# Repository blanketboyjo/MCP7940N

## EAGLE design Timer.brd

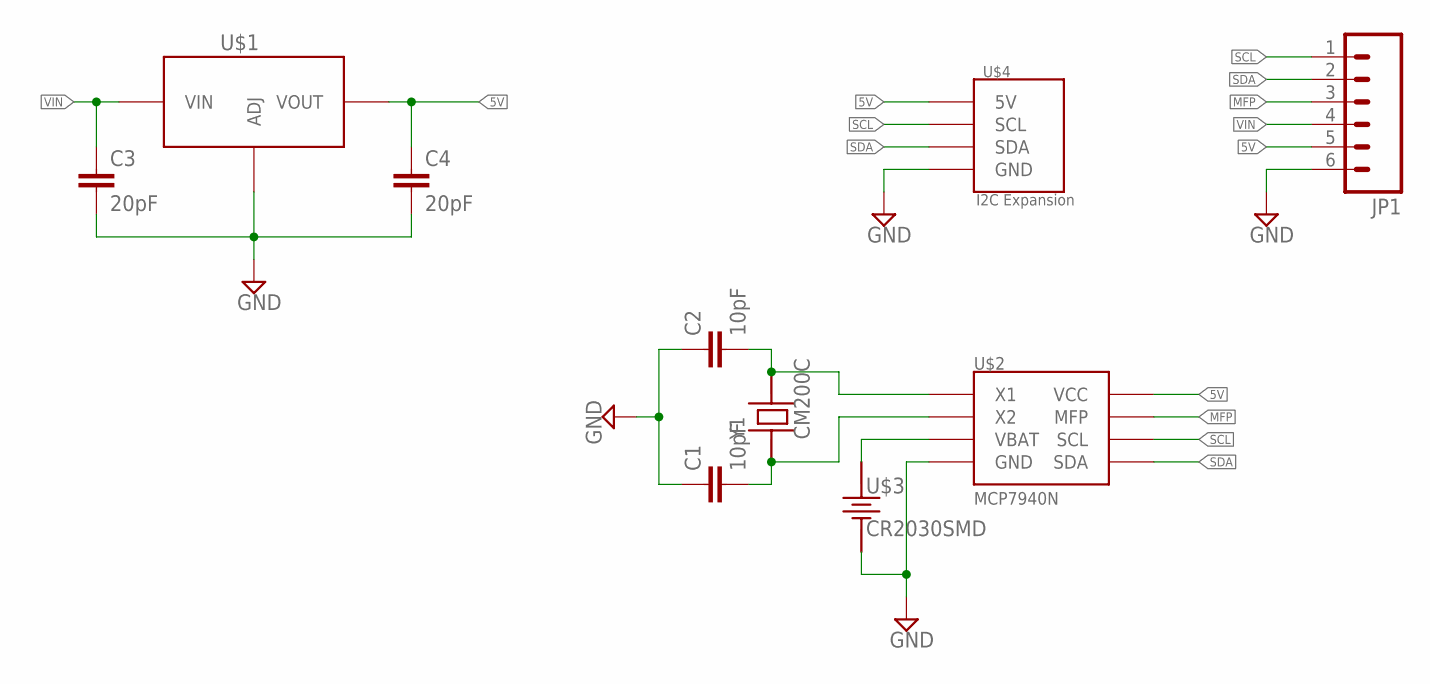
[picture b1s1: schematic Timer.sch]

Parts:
C1, C2: 10pF; 0603-CAP
C3, C4: 20pF; 0603-CAP
JP1: M06SILK_FEMALE_PTH; 1X06
U$1: LM1117; SOT223
U$2: MCP7940NSOIC-8; SOIC-8
U$3: CR2030SMD
U$4: I2CEXPANSION; JST-4-PTH-VERT
Y1: CM200C; CM2##

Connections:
5V: C4.1, JP1.5, U$1.P2 (VOUT), U$1.P4 (VOUT), U$2.VCC, U$4.1 (5V)
GND: C1.1, C2.1, C3.2, C4.2, JP1.6, U$1.P1 (ADJ), U$2.GND, U$3.GND (NEG), U$3.GND1 (NEG), U$4.4 (GND)
MFP: JP1.3, U$2.MFP
unnamed: U$2.VBAT, U$3.POS
unnamed: C2.2, U$2.X1, Y1.4
unnamed: C1.2, U$2.X2, Y1.1
SCL: JP1.1, U$2.SCL, U$4.2 (SCL)
SDA: JP1.2, U$2.SDA, U$4.3 (SDA)
VIN: C3.1, JP1.4, U$1.P3 (VIN)

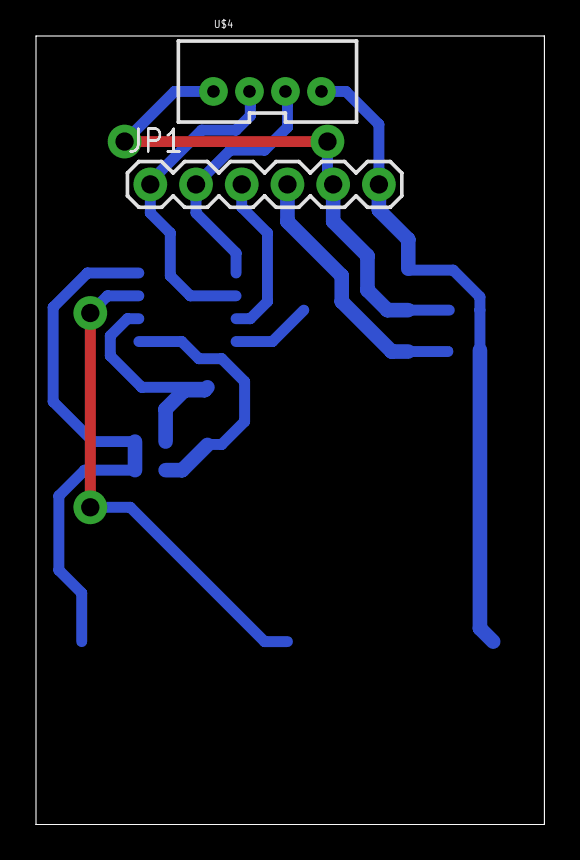
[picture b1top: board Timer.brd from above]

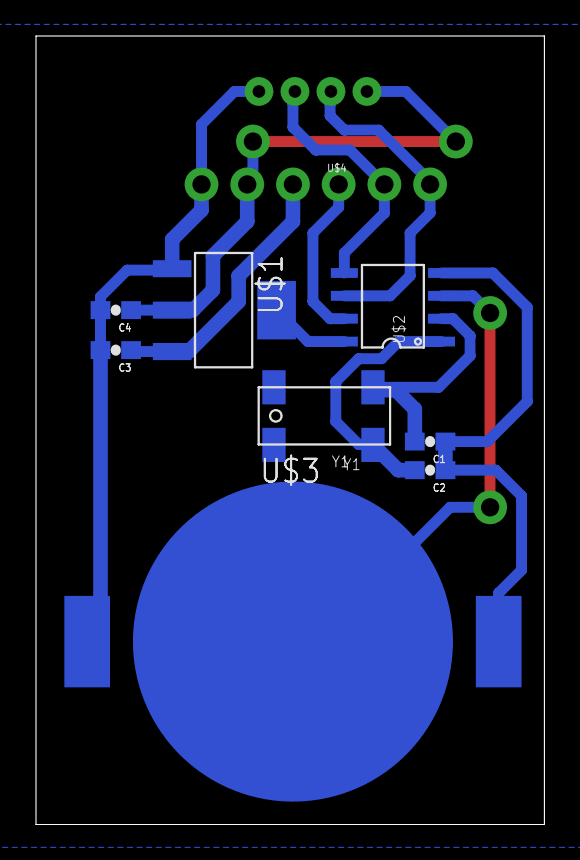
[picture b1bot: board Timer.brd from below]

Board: 2 copper layers, 28.2 x 43.8 mm, 10 parts (8 on the bottom side), 9 nets.

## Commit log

2015-08-17 :confetti_ball: Added .gitattributes & .gitignore files
2015-08-17 Version 1.0
    This is the first version, which is unlabelled due to hasty designing.
2015-08-17 Updated ignore
    Removed eagle.epf

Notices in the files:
parts and their libraries:
SparkFun-Capacitors: Licensing: Creative Commons ShareAlike 4.0 International - https://creativecommons.org/licenses/by-sa/4.0
